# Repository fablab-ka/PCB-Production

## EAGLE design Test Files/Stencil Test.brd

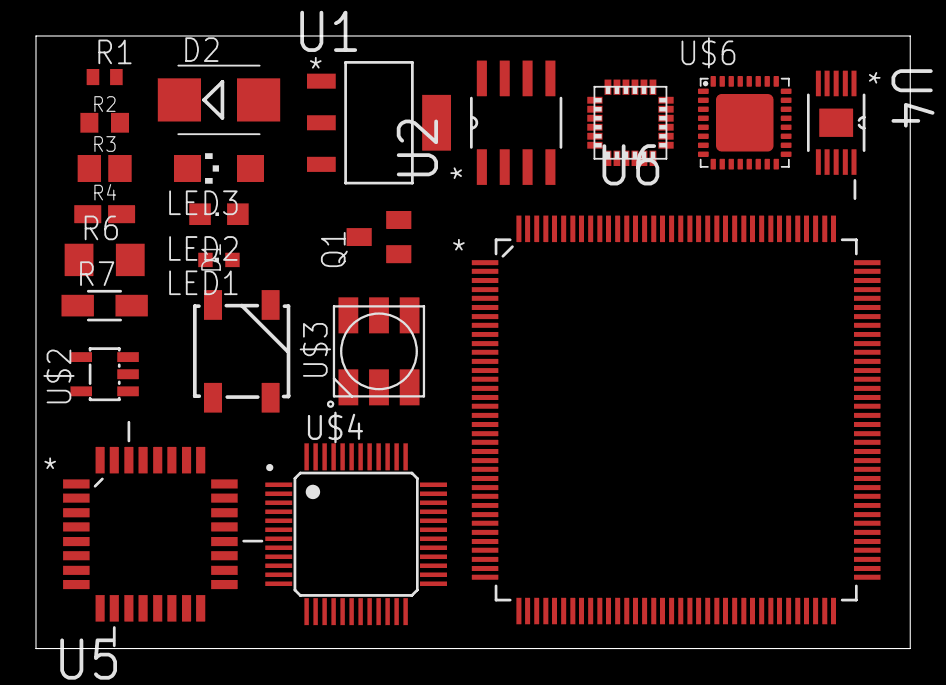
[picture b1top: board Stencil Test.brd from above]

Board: 2 copper layers, 48.6 x 34.0 mm, 22 parts (0 on the bottom side), 4 nets, no tracks yet.

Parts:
D1: WS2812B
D2: ES2D; SMB
LED1: CHIPLED_0603
LED2: CHIPLED_0805
LED3: CHIPLED_1206
Q1: BC817-16LT1_NPN_SMD; SOT23-BEC
R1: R0402
R2: R0603
R3: R0805
R4: R0805W
R6: R1206
R7: R1206W
U1: LM1117MP-ADJ; SOT230P696X180-4N
U2: MC33063AD; SOIC127P600X175-8N
U4: XTR111AIDGQT; SOP50P490X120-15N
U5: ATMEGA328P-AU; QFP80P900X900X120-32N
U6: ATSAM3X8EA-AU; QFP50P2200X2200X145-144N
U$2: TPS73133; SOT23-5L
U$3: APA102; LED5050
U$4: STM32F042C6T6; LQFP48
U$5: MPU-9150.QFN; QFN.24.4X4
U$6: ATSAMD21E18A-MUT; QFN32

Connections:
VCC: U2.6, U5.6
VDDCORE: U6.10, U6.45, U6.124
VDDCORE_2: U6.61, U6.104
VDDIO: U6.11, U6.62, U6.125

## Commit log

2016-12-30 stencil test board
